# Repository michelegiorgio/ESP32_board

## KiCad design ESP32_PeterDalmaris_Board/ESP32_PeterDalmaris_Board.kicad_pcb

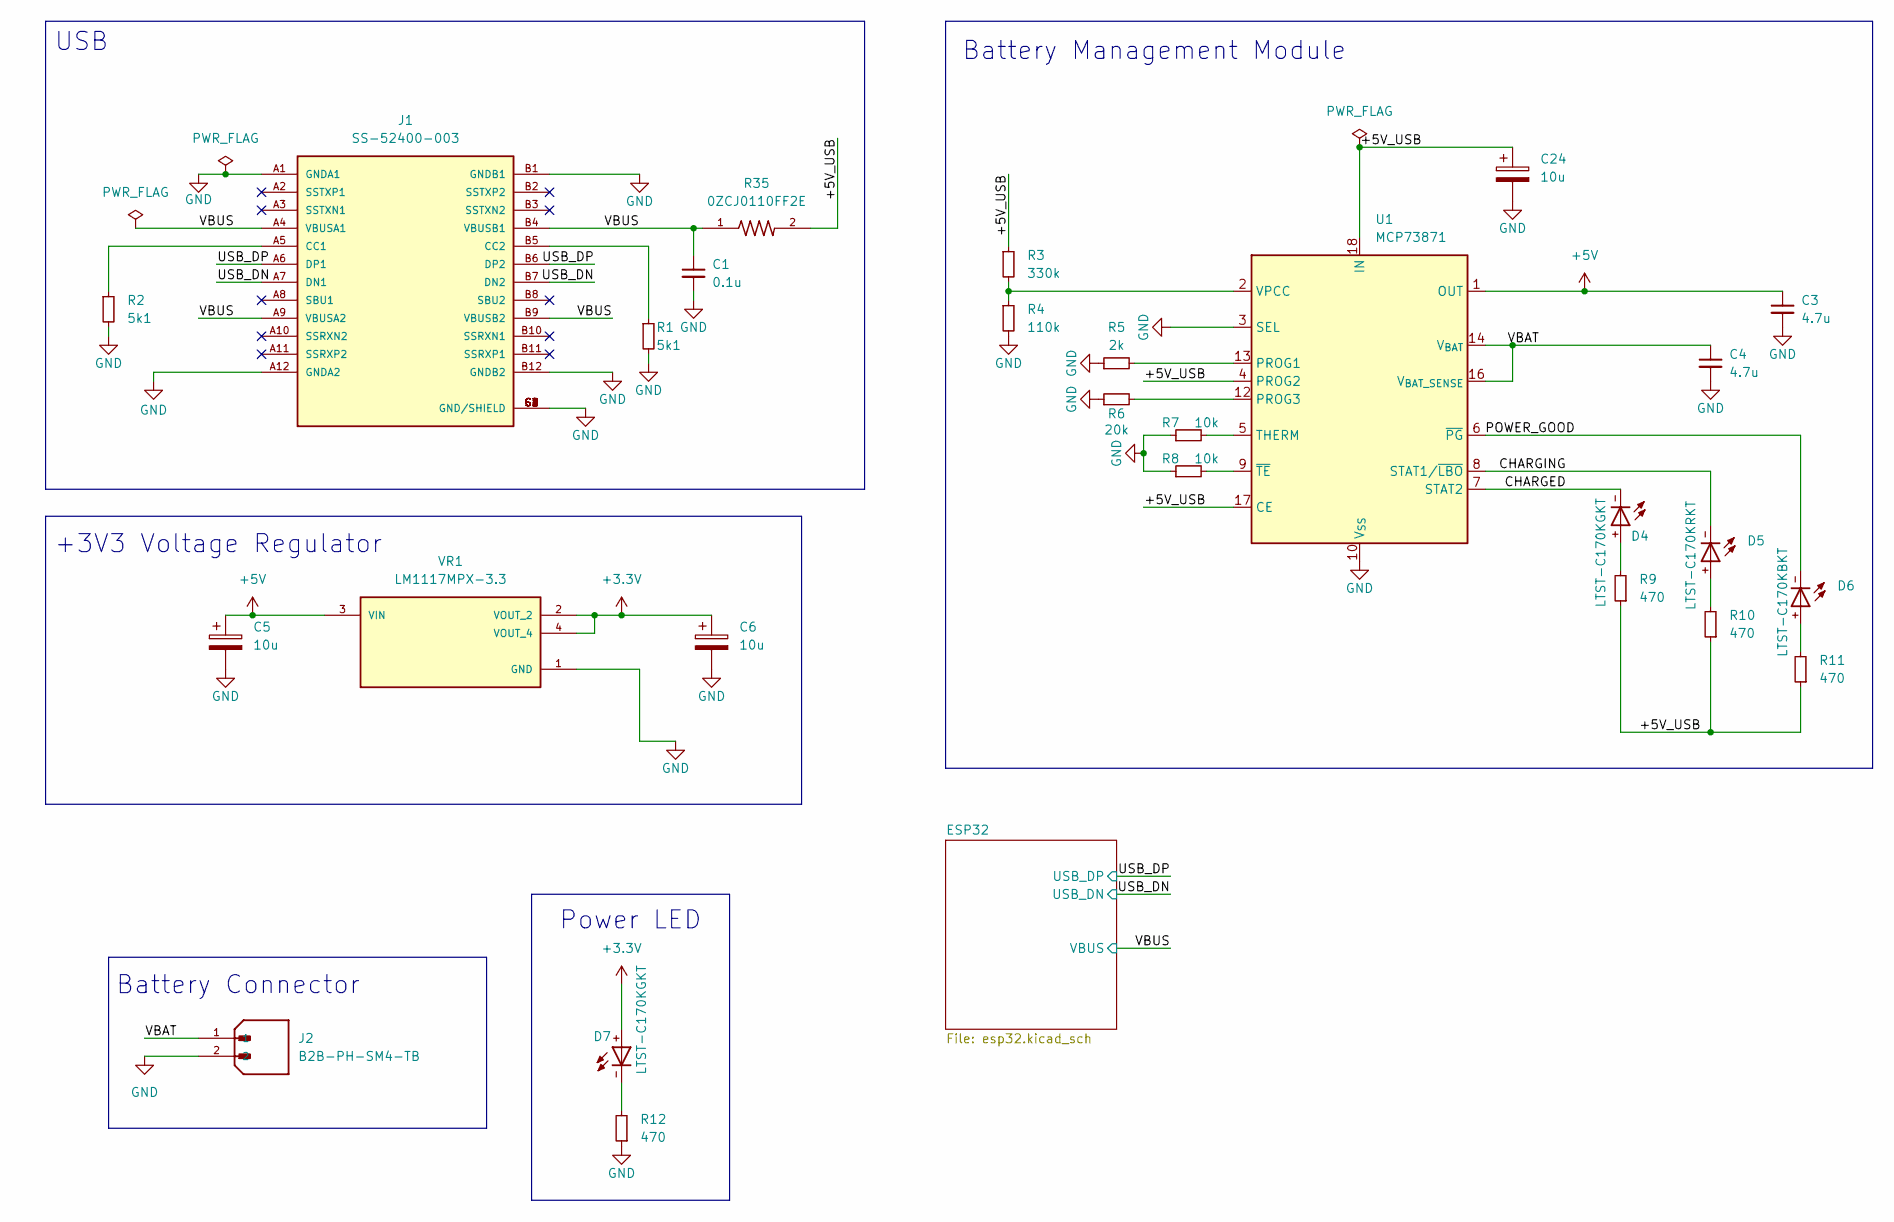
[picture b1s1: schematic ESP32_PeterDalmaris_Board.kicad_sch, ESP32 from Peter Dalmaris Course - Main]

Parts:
C1: 0.1u; C_0805_2012Metric
C3, C4: 4.7u; C_0805_2012Metric
C5, C6, C24: 10u; CAPMP3216X180N
D4, D7: LTST-C170KGKT; DIOC200X125X110
D5: LTST-C170KRKT; DIOC200X125X110
D6: LTST-C170KBKT; DIOC200X125X110
J1: SS-52400-003; BELFUSE_SS-52400-003; PARTREV A0
J2: B2B-PH-SM4-TB; JST_B2B-PH-SM4-TB; PARTREV N/A
R1, R2: 5k1; R_0805_2012Metric
R3: 330k; R_0805_2012Metric
R4: 110k; R_0805_2012Metric
R5: 2k; R_0805_2012Metric
R6: 20k; R_0805_2012Metric
R7, R8: 10k; R_0805_2012Metric
R9, R10, R11, R12: 470; R_0805_2012Metric
R35: 0ZCJ0110FF2E
U1: MCP73871; QFN-20-1EP_4x4mm_P0.5mm_EP2.5x2.5mm
VR1: LM1117MPX-3.3; VREG_LM1117MPX-3.3; PARTREV O

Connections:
+3.3V: C6.1, D7.+, VR1.2 (VOUT_2), VR1.4 (VOUT_4); also elsewhere on the board
+5V: C3.1, C5.1, U1.1 (OUT), U1.20 (OUT), VR1.3 (VIN)
/+5V_USB: C24.1, R3.1, R9.1, R10.1, R11.1, R35.2, U1.4 (PROG2), U1.17 (CE), U1.18 (IN), U1.19 (IN)
/CHARGED: D4.-, U1.7 (STAT2)
/CHARGING: D5.-, U1.8 (STAT1/~LBO)
/POWER_GOOD: D6.-, U1.6 (~PG)
/USB_DN: J1.A7 (DN1), J1.B7 (DN2); also elsewhere on the board
/USB_DP: J1.A6 (DP1), J1.B6 (DP2); also elsewhere on the board
/VBAT: C4.1, J2.1, U1.14 (V_{BAT}), U1.15 (V_{BAT}), U1.16 (V_{BAT_SENSE})
/VBUS: C1.1, J1.A4 (VBUSA1), J1.A9 (VBUSA2), J1.B4 (VBUSB1), J1.B9 (VBUSB2), R35.1; also elsewhere on the board
GND: C1.2, C3.2, C4.2, C5.2, C6.2, C24.2, J1.A1 (GNDA1), J1.A12 (GNDA2), J1.B1 (GNDB1), J1.B12 (GNDB2), J1.G1 (GND/SHIELD), J1.G2 (GND/SHIELD), J1.G3 (GND/SHIELD), J1.G4 (GND/SHIELD), J1.S1 (GND/SHIELD), J1.S2 (GND/SHIELD), J1.S3 (GND/SHIELD), J1.S4 (GND/SHIELD), J2.2, R1.2, R2.2, R4.2, R5.1, R6.1, R7.1, R8.1, R12.1, U1.3 (SEL), U1.10 (V_{SS}), U1.11 (V_{SS}), U1.21 (V_{SS}), VR1.1 (GND); also elsewhere on the board
unnamed: D4.+, R9.2
unnamed: D5.+, R10.2
unnamed: D6.+, R11.2
unnamed: D7.-, R12.2
unnamed: J1.A5 (CC1), R2.1
unnamed: J1.B5 (CC2), R1.1
unnamed: R5.2, U1.13 (PROG1)
unnamed: R6.2, U1.12 (PROG3)
unnamed: R7.2, U1.5 (THERM)
unnamed: R3.2, R4.1, U1.2 (VPCC)
unnamed: R8.2, U1.9 (~TE)

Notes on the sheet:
+3V3 Voltage Regulator
Battery Connector
Power LED
Battery Management Module
USB

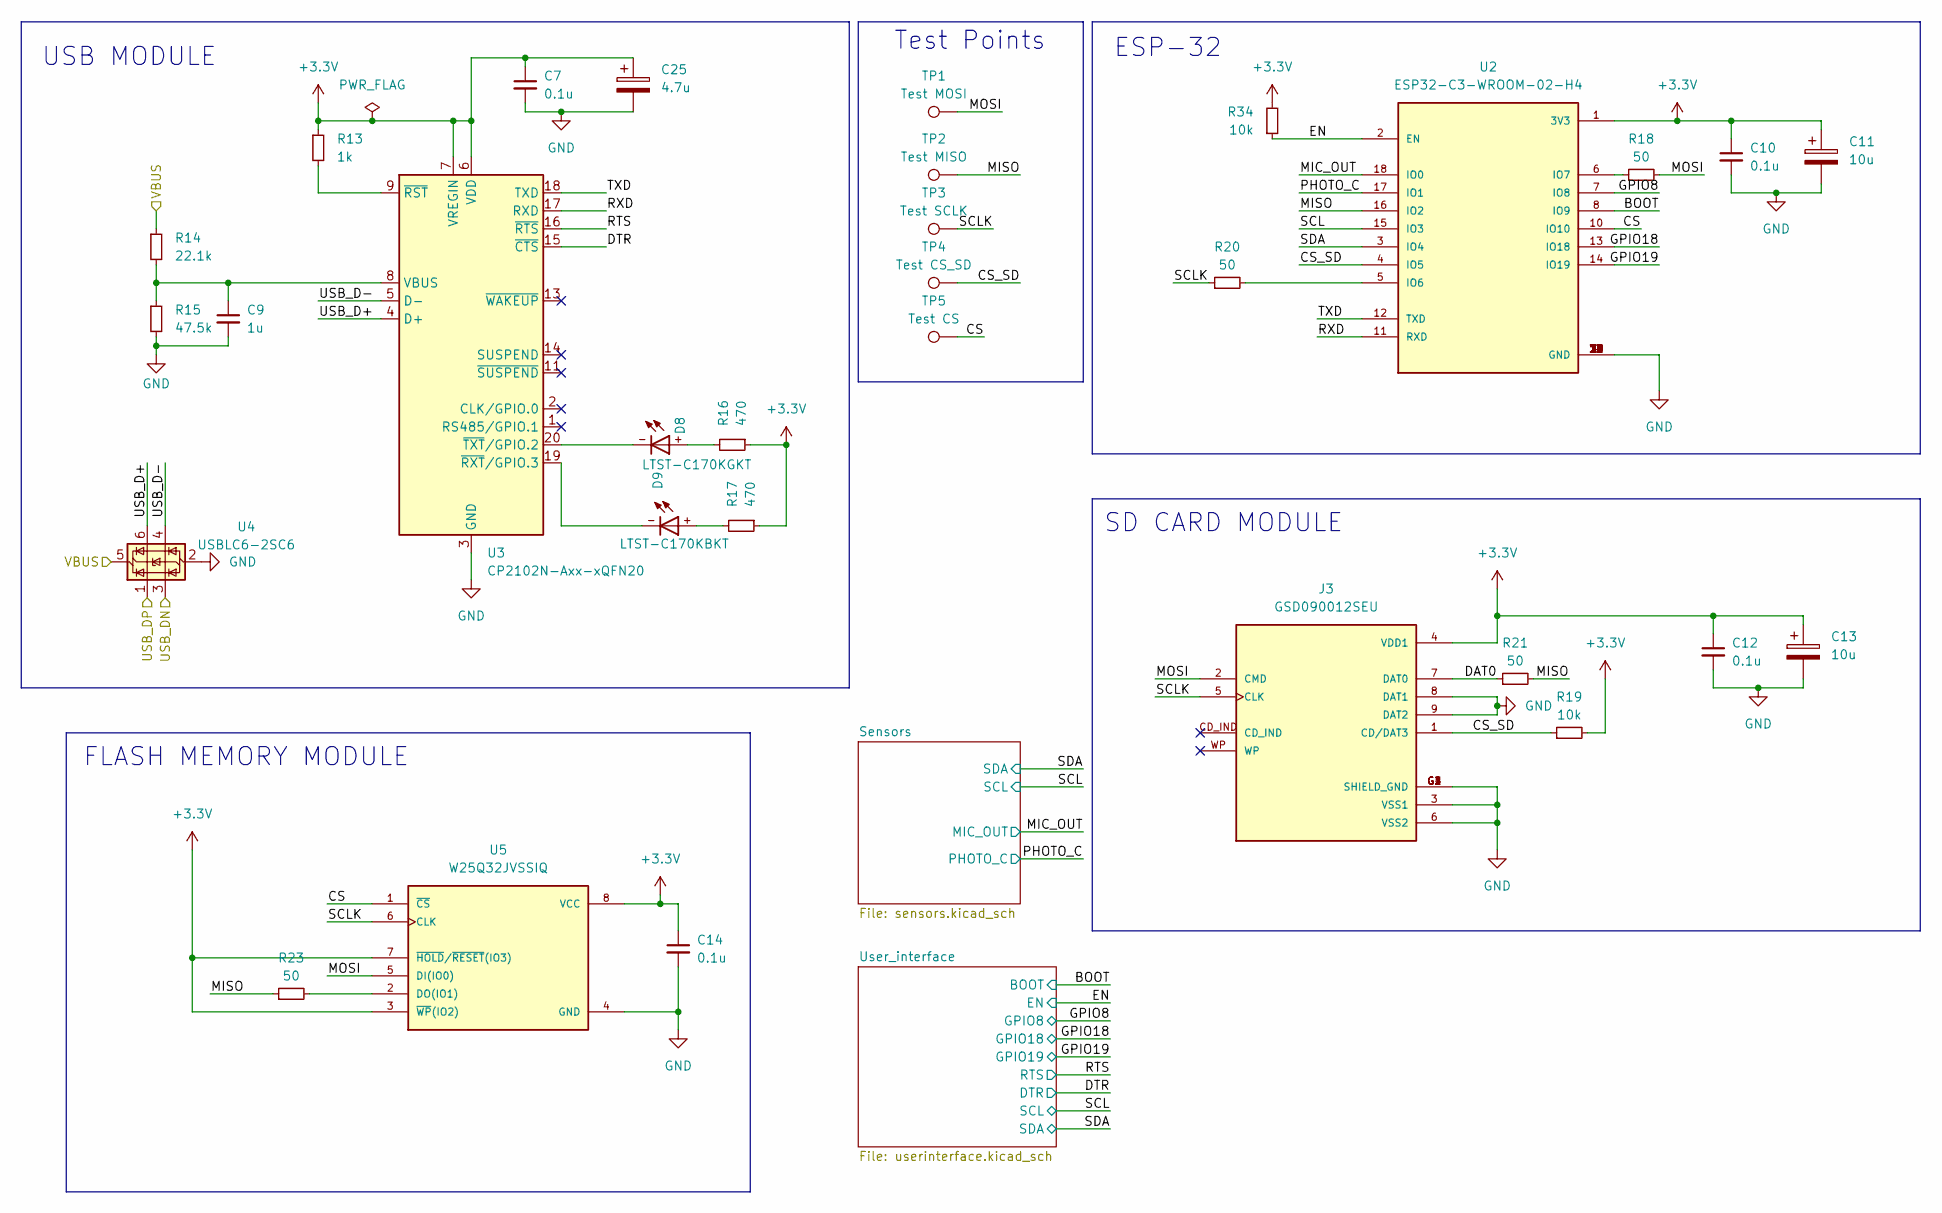
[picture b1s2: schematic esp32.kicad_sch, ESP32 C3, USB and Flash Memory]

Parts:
C7, C10, C12, C14: 0.1u; C_0805_2012Metric
C9: 1u; C_0805_2012Metric
C11, C13: 10u; CAPMP3216X180N
C25: 4.7u; CAPMP3216X180N
D8: LTST-C170KGKT; DIOC200X125X110
D9: LTST-C170KBKT; DIOC200X125X110
J3: GSD090012SEU; AMPHENOL_GSD090012SEU; PARTREV E
R13: 1k; R_0805_2012Metric
R14: 22.1k; R_0805_2012Metric
R15: 47.5k; R_0805_2012Metric
R16, R17: 470; R_0805_2012Metric
R18, R20, R21, R23: 50; R_0805_2012Metric
R19, R34: 10k; R_0805_2012Metric
TP1: Test MOSI; TestPoint_Pad_D1.0mm
TP2: Test MISO; TestPoint_Pad_D1.0mm
TP3: Test SCLK; TestPoint_Pad_D1.0mm
TP4: Test CS_SD; TestPoint_Pad_D1.0mm
TP5: Test CS; TestPoint_Pad_D1.0mm
U2: ESP32-C3-WROOM-02-H4; MODULE_ESP32-C3-WROOM-02-H4
U3: CP2102N-Axx-xQFN20; SiliconLabs_QFN-20-1EP_3x3mm_P0.5mm_EP1.8x1.8mm
U4: USBLC6-2SC6; SOT-23-6
U5: W25Q32JVSSIQ; SOIC127P790X216-8N; M_PART_NUMBER W25QXX

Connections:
+3.3V: C7.1, C10.1, C11.1, C12.1, C13.1, C14.1, C25.1, J3.4 (VDD1), R13.1, R16.1, R17.1, R19.2, R34.2, U2.1 (3V3), U3.6 (VDD), U3.7 (VREGIN), U5.3 (~WP(IO2)), U5.7 (~HOLD/~RESET(IO3)), U5.8 (VCC); also elsewhere on the board
/ESP32/BOOT: U2.8 (IO9); also elsewhere on the board
/ESP32/CS: TP5.1, U2.10 (IO10), U5.1 (~CS)
/ESP32/CS_SD: J3.1 (CD/DAT3), R19.1, TP4.1, U2.4 (IO5)
/ESP32/DAT0: J3.7 (DAT0), R21.1
/ESP32/DTR: U3.15 (~CTS); also elsewhere on the board
/ESP32/EN: R34.1, U2.2 (EN); also elsewhere on the board
/ESP32/GPIO8: U2.7 (IO8); also elsewhere on the board
/ESP32/GPIO18: U2.13 (IO18); also elsewhere on the board
/ESP32/GPIO19: U2.14 (IO19); also elsewhere on the board
/ESP32/MIC_OUT: U2.18 (IO0); also elsewhere on the board
/ESP32/MISO: R21.2, R23.1, TP2.1, U2.16 (IO2)
/ESP32/MOSI: J3.2 (CMD), R18.2, TP1.1, U5.5 (DI(IO0))
/ESP32/PHOTO_C: U2.17 (IO1); also elsewhere on the board
/ESP32/RTS: U3.16 (~RTS); also elsewhere on the board
/ESP32/RXD: U2.11 (RXD), U3.17 (RXD)
/ESP32/SCL: U2.15 (IO3); also elsewhere on the board
/ESP32/SCLK: J3.5 (CLK), R20.1, TP3.1, U5.6 (CLK)
/ESP32/SDA: U2.3 (IO4); also elsewhere on the board
/ESP32/TXD: U2.12 (TXD), U3.18 (TXD)
/ESP32/USB_D+: U3.4 (D+), U4.6 (I/O1)
/ESP32/USB_D-: U3.5 (D-), U4.4 (I/O2)
/USB_DN: U4.3 (I/O2); also elsewhere on the board
/USB_DP: U4.1 (I/O1); also elsewhere on the board
/VBUS: R14.1, U4.5 (VBUS); also elsewhere on the board
GND: C7.2, C9.2, C10.2, C11.2, C12.2, C13.2, C14.2, C25.2, J3.3 (VSS1), J3.6 (VSS2), J3.8 (DAT1), J3.9 (DAT2), J3.G1 (SHIELD_GND), J3.G2 (SHIELD_GND), J3.G3 (SHIELD_GND), J3.G4 (SHIELD_GND), R15.2, U2.9 (GND), U2.19 (GND), U2.20 (GND), U2.21 (GND), U2.22 (GND), U2.23 (GND), U2.24 (GND), U2.25 (GND), U2.26 (GND), U2.27 (GND), U2.28 (GND), U2.29 (GND), U2.30 (GND), U2.31 (GND), U2.32 (GND), U2.33 (GND), U2.34 (GND), U2.35 (GND), U2.36 (GND), U2.37 (GND), U2.38 (GND), U2.39 (GND), U3.3 (GND), U3.12 (GND), U3.21 (GND), U4.2 (GND), U5.4 (GND); also elsewhere on the board
unnamed: D8.+, R16.2
unnamed: D9.+, R17.2
unnamed: R20.2, U2.5 (IO6)
unnamed: R18.1, U2.6 (IO7)
unnamed: C9.1, R14.2, R15.1, U3.8 (VBUS)
unnamed: R13.2, U3.9 (~RST)
unnamed: D9.-, U3.19 (~RXT/GPIO.3)
unnamed: D8.-, U3.20 (~TXT/GPIO.2)
unnamed: R23.2, U5.2 (DO(IO1))

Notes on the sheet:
USB MODULE
SD CARD MODULE
FLASH MEMORY MODULE
ESP-32
Test Points

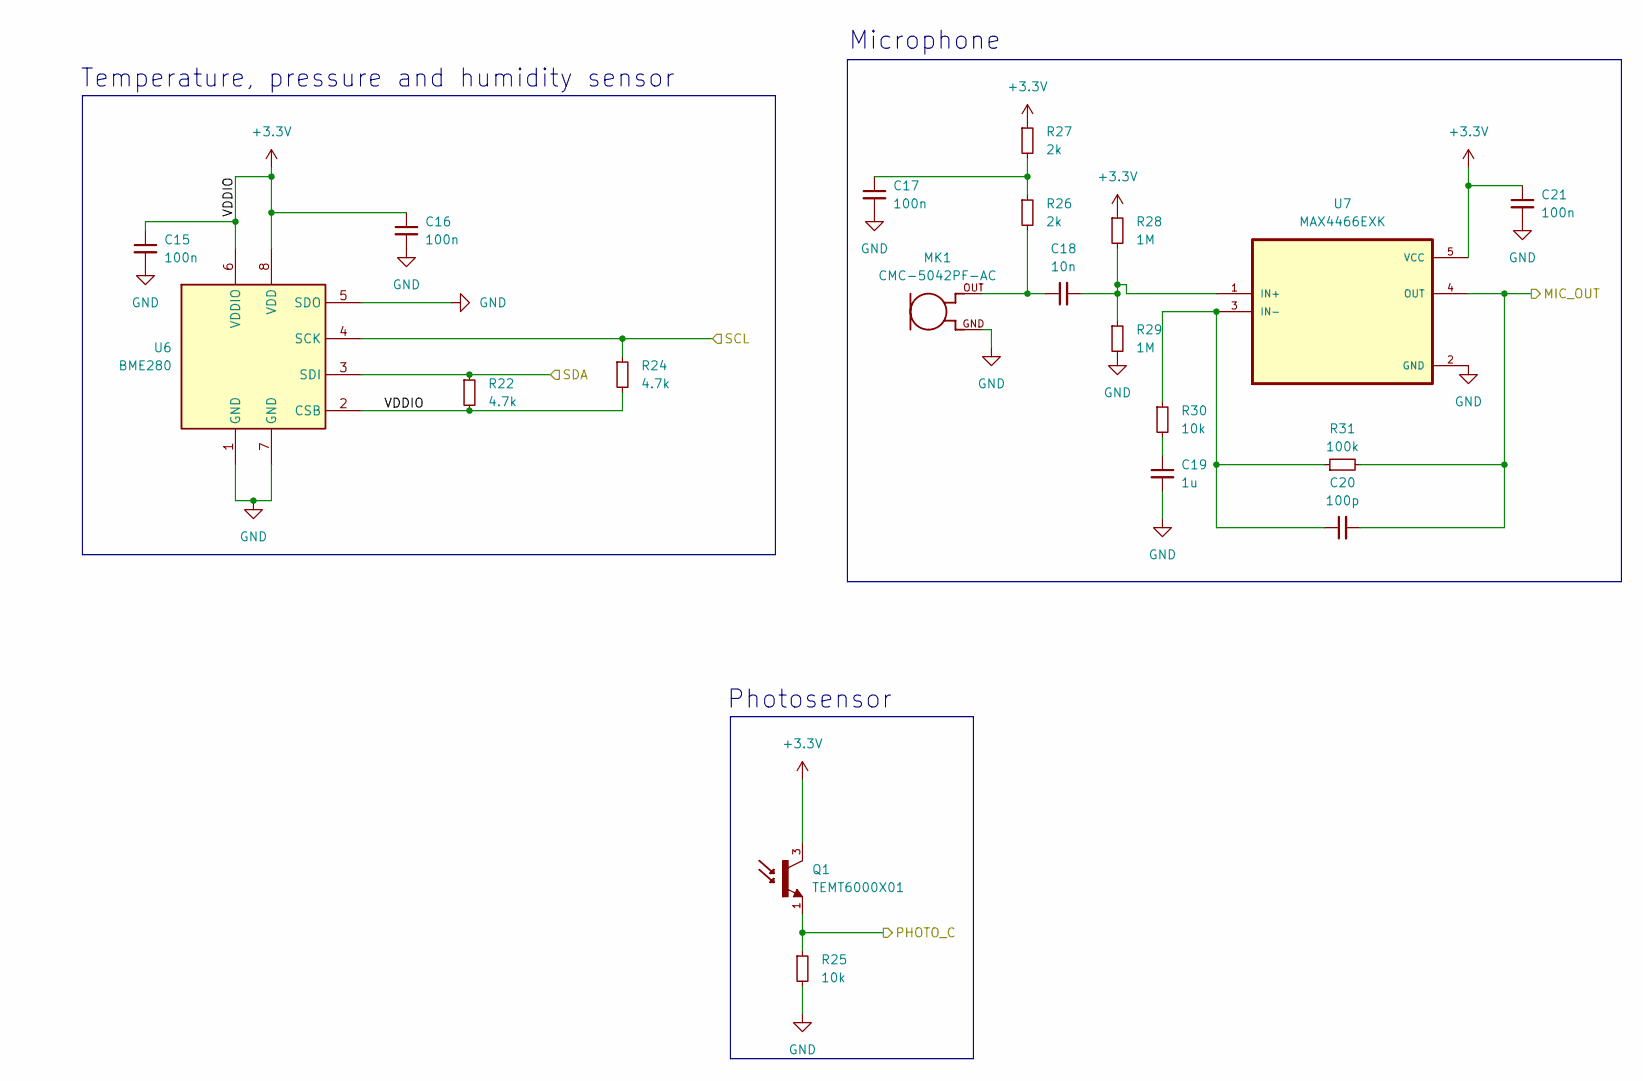
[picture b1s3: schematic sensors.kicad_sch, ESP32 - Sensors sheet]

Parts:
C15, C16, C17, C21: 100n; C_0805_2012Metric
C18: 10n; C_0805_2012Metric
C19: 1u; C_0805_2012Metric
C20: 100p; C_0805_2012Metric
MK1: CMC-5042PF-AC; CUI_CMC-5042PF-AC
Q1: TEMT6000X01; TRANS_TEMT6000X01; PARTREV 1.9
R22, R24: 4.7k; R_0805_2012Metric
R25, R30: 10k; R_0805_2012Metric
R26, R27: 2k; R_0805_2012Metric
R28, R29: 1M; R_0805_2012Metric
R31: 100k; R_0805_2012Metric
U6: BME280; Bosch_LGA-8_2.5x2.5mm_P0.65mm_ClockwisePinNumbering
U7: MAX4466EXK; SOT65P210X110-5N

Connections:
+3.3V: C15.1, C16.1, C21.1, Q1.3, R22.2, R24.2, R27.1, R28.1, U6.2 (CSB), U6.6 (VDDIO), U6.8 (VDD), U7.5 (VCC); also elsewhere on the board
/ESP32/MIC_OUT: C20.2, R31.2, U7.4 (OUT); also elsewhere on the board
/ESP32/PHOTO_C: Q1.1, R25.1; also elsewhere on the board
/ESP32/SCL: R24.1, U6.4 (SCK); also elsewhere on the board
/ESP32/SDA: R22.1, U6.3 (SDI); also elsewhere on the board
GND: C15.2, C16.2, C17.2, C19.2, C21.2, MK1.GND, R25.2, R29.2, U6.1 (GND), U6.5 (SDO), U6.7 (GND), U7.2 (GND); also elsewhere on the board
unnamed: C17.1, R26.1, R27.2
unnamed: C18.1, MK1.OUT, R26.2
unnamed: C19.1, R30.2
unnamed: C18.2, R28.2, R29.1, U7.1 (IN+)
unnamed: C20.1, R30.1, R31.1, U7.3 (IN-)

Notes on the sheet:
Photosensor
Microphone
Temperature, pressure and humidity sensor

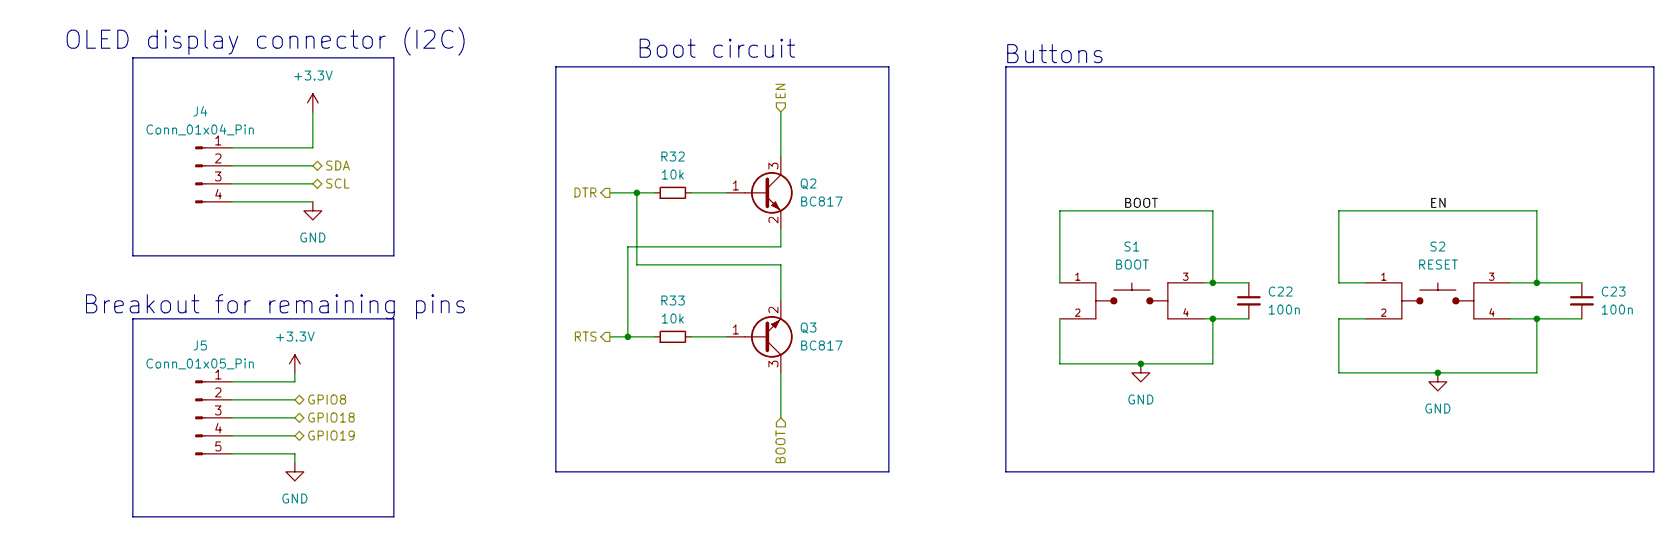
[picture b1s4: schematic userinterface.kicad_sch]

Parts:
C22, C23: 100n; C_0805_2012Metric
J4: Conn_01x04_Pin; PinHeader_1x04_P2.54mm_Vertical
J5: Conn_01x05_Pin; PinHeader_1x05_P2.54mm_Vertical
Q2, Q3: BC817; SOT-23
R32, R33: 10k; R_0805_2012Metric
S1: BOOT; SW_TL3305AF260QG; PARTREV C
S2: RESET; SW_TL3305AF260QG; PARTREV C

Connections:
+3.3V: J4.1, J5.1; also elsewhere on the board
/ESP32/BOOT: C22.1, Q3.3 (C), S1.1, S1.3; also elsewhere on the board
/ESP32/DTR: Q3.2 (E), R32.1; also elsewhere on the board
/ESP32/EN: C23.1, Q2.3 (C), S2.1, S2.3; also elsewhere on the board
/ESP32/GPIO8: J5.2; also elsewhere on the board
/ESP32/GPIO18: J5.3; also elsewhere on the board
/ESP32/GPIO19: J5.4; also elsewhere on the board
/ESP32/RTS: Q2.2 (E), R33.1; also elsewhere on the board
/ESP32/SCL: J4.3; also elsewhere on the board
/ESP32/SDA: J4.2; also elsewhere on the board
GND: C22.2, C23.2, J4.4, J5.5, S1.2, S1.4, S2.2, S2.4; also elsewhere on the board
unnamed: Q2.1 (B), R32.2
unnamed: Q3.1 (B), R33.2

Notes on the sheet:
Boot circuit
OLED display connector (I2C)
Breakout for remaining pins
Buttons

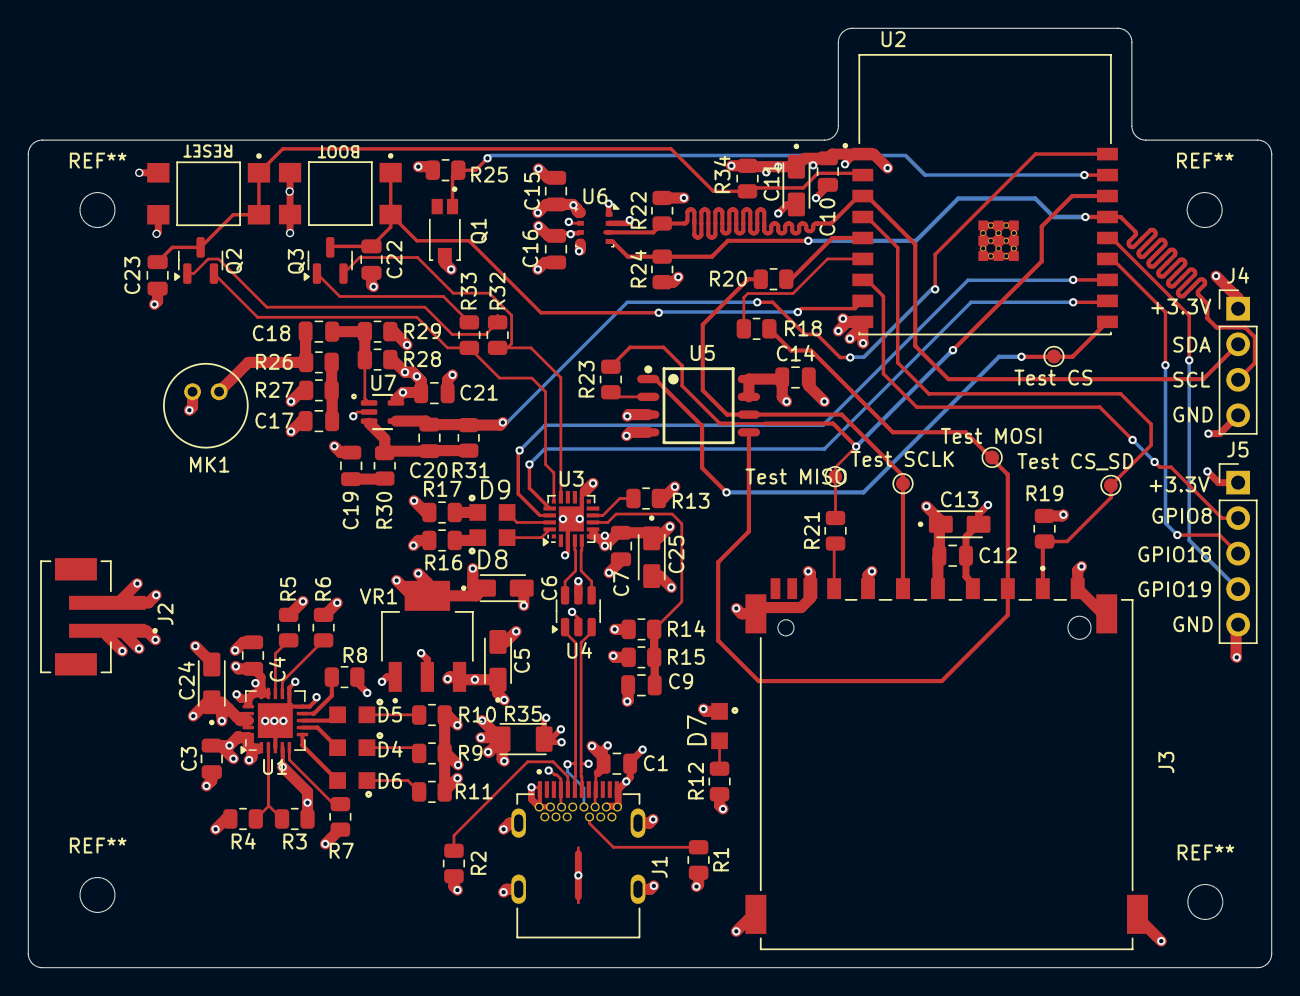
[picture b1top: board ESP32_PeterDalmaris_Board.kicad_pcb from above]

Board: 4 copper layers, 89.0 x 67.2 mm, 88 parts (0 on the bottom side), 59 nets.
